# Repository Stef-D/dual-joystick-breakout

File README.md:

dual-joystick-breakout
======================
Dual PS2-style joystick breakout.

Based on Sparkfun.com 's breakout board (https://www.sparkfun.com/products/9110), so all credits to them.

1 -> VCC

2 -> Vertical - left

3 -> Horizontal - left

4 -> Select/push - left

5 -> GND

6 -> Vertical - right

7 -> Horizontal - right

8 -> Select/push - right

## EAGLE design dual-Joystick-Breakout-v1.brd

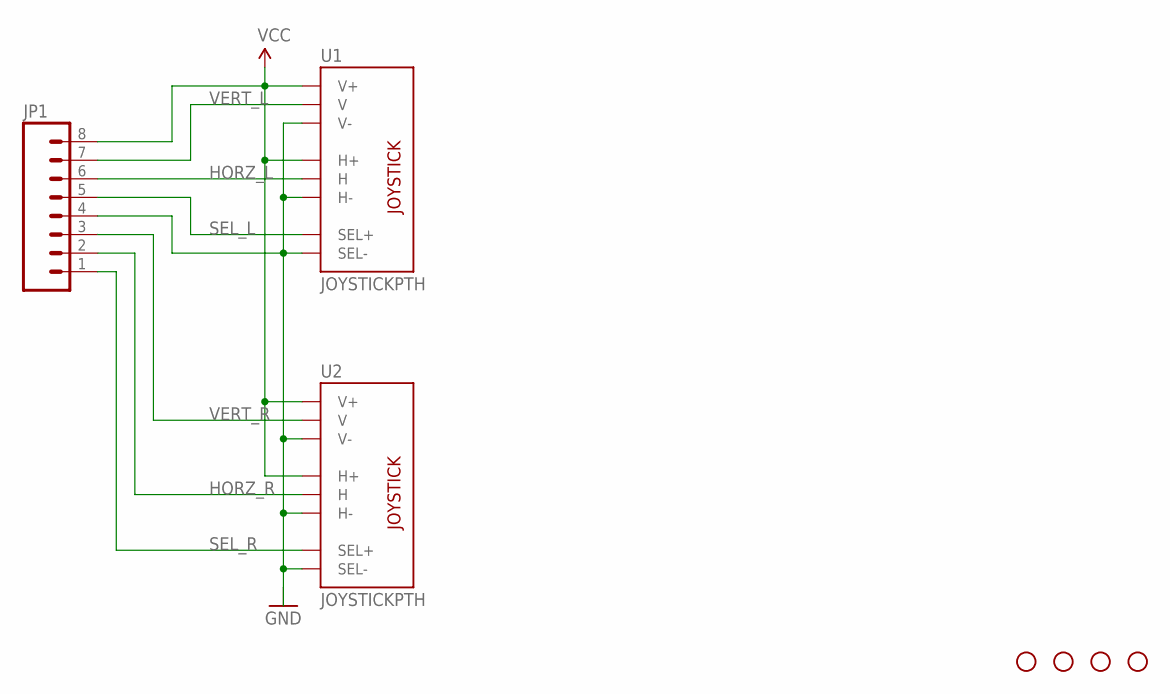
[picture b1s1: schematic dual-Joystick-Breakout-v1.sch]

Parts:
JP1: M081X08; 1X08
U1, U2: JOYSTICKPTH; JOYSTICK
U$3, U$4, U$5, U$6: STAND-OFF

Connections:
GND: JP1.4, U1.B2A (SEL-), U1.H3 (H-), U1.V3 (V-), U2.B2A (SEL-), U2.H3 (H-), U2.V3 (V-)
HORZ_L: JP1.6, U1.H2 (H)
HORZ_R: JP1.2, U2.H2 (H)
SEL_L: JP1.5, U1.B1A (SEL+)
SEL_R: JP1.1, U2.B1A (SEL+)
VCC: JP1.8, U1.H1 (H+), U1.V1 (V+), U2.H1 (H+), U2.V1 (V+)
VERT_L: JP1.7, U1.V2 (V)
VERT_R: JP1.3, U2.V2 (V)

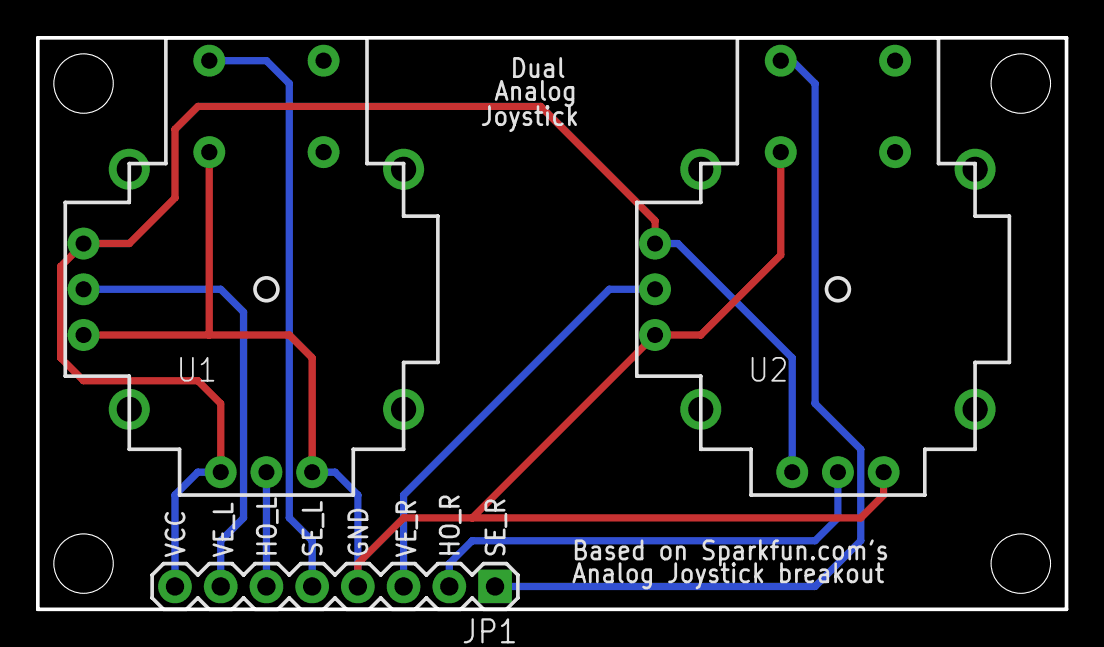
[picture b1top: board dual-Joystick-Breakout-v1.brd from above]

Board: 2 copper layers, 57.1 x 31.8 mm, 7 parts (0 on the bottom side), 8 nets.

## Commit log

2014-05-21 Updated readme (styling derp)

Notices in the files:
parts and their libraries:
SparkFun-Connectors: Licensing: CC v3.0 Share-Alike You are welcome to use this library for commercial purposes.
